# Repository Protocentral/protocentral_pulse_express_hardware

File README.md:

# ProtoCentral Pulse Express — Hardware

Open-source hardware design files for the **ProtoCentral Pulse Express** pulse-oximetry / heart-rate breakout — pairing the [Maxim MAX30102](https://www.analog.com/en/products/max30102.html) optical sensor with the [Maxim MAX32664D](https://www.analog.com/en/products/max32664.html) biometric sensor hub.

Unlike our [Pulse](https://github.com/Protocentral/protocentral_pulse_hardware) board, which streams raw PPG for the host to process, Pulse Express runs Maxim's algorithms on the MAX32664D hub itself and returns computed heart rate, SpO₂, and blood-pressure-trend estimates over I²C. That offloads the signal processing from your MCU at the cost of visibility into the raw signal.

## Links

| | |
|---|---|
| 🛒 Product page | https://protocentral.com/product/pulse-express-pulse-ox-heart-rate-sensor-with-max32664/ |
| 💻 Arduino library | https://github.com/Protocentral/protocentral-pulse-express |
| 📄 Sensor hub datasheet (Analog Devices / Maxim) | https://www.analog.com/media/en/technical-documentation/data-sheets/MAX32664.pdf |
| 📄 Optical sensor datasheet | https://www.analog.com/media/en/technical-documentation/data-sheets/MAX30102.pdf |

## Specifications

- **Sensor hub:** Maxim MAX32664GTGD+ (MAX32664D variant) with 32.768 kHz crystal
- **Optical sensor:** Maxim MAX30102 — red (660 nm) + IR (880 nm) LEDs, photodiode, and AFE
- **Output:** computed heart rate, SpO₂, and blood-pressure trend from the on-hub algorithms
- **Interface:** I²C, via 2× TXS0102 bidirectional level translators
- **Connector:** 6-pin 0.1″ header
- **Supply:** onboard AP2112K-3.3 V and AP2112K-1.8 V LDOs
- **Board:** 36.0 × 17.5 mm, 2-layer

## Revisions

| Revision | Design files | Notes |
|---|---|---|
| **v3** (current) | [`hardware/`](hardware/) | KiCad 10 |
| earlier | [`protocentral-pulse-express/hardware/`](https://github.com/Protocentral/protocentral-pulse-express/tree/master/hardware) | Eagle; retained in the Arduino library repository so existing links keep working |

## Repository layout

| Folder | Contents |
|---|---|
| [`hardware/`](hardware/) | KiCad project (schematic + PCB layout) and the exported [schematic PDF](hardware/protocentral-pulse-express-v3-schematic.pdf) |

## Important notice

This device is intended for research, education, and evaluation use only. It is **not** a medical diagnostic instrument and is not FDA, CE, or FCC approved for consumer use. The blood-pressure-trend output of the MAX32664D requires per-user calibration and is not a substitute for a validated blood-pressure monitor.

## License

The hardware design files in this repository are licensed under the **CERN Open Hardware Licence Version 2 – Permissive (CERN-OHL-P v2)**. See [LICENSE](LICENSE).

The accompanying firmware/library (in the separate [protocentral-pulse-express](https://github.com/Protocentral/protocentral-pulse-express) repository) is licensed under the MIT License.

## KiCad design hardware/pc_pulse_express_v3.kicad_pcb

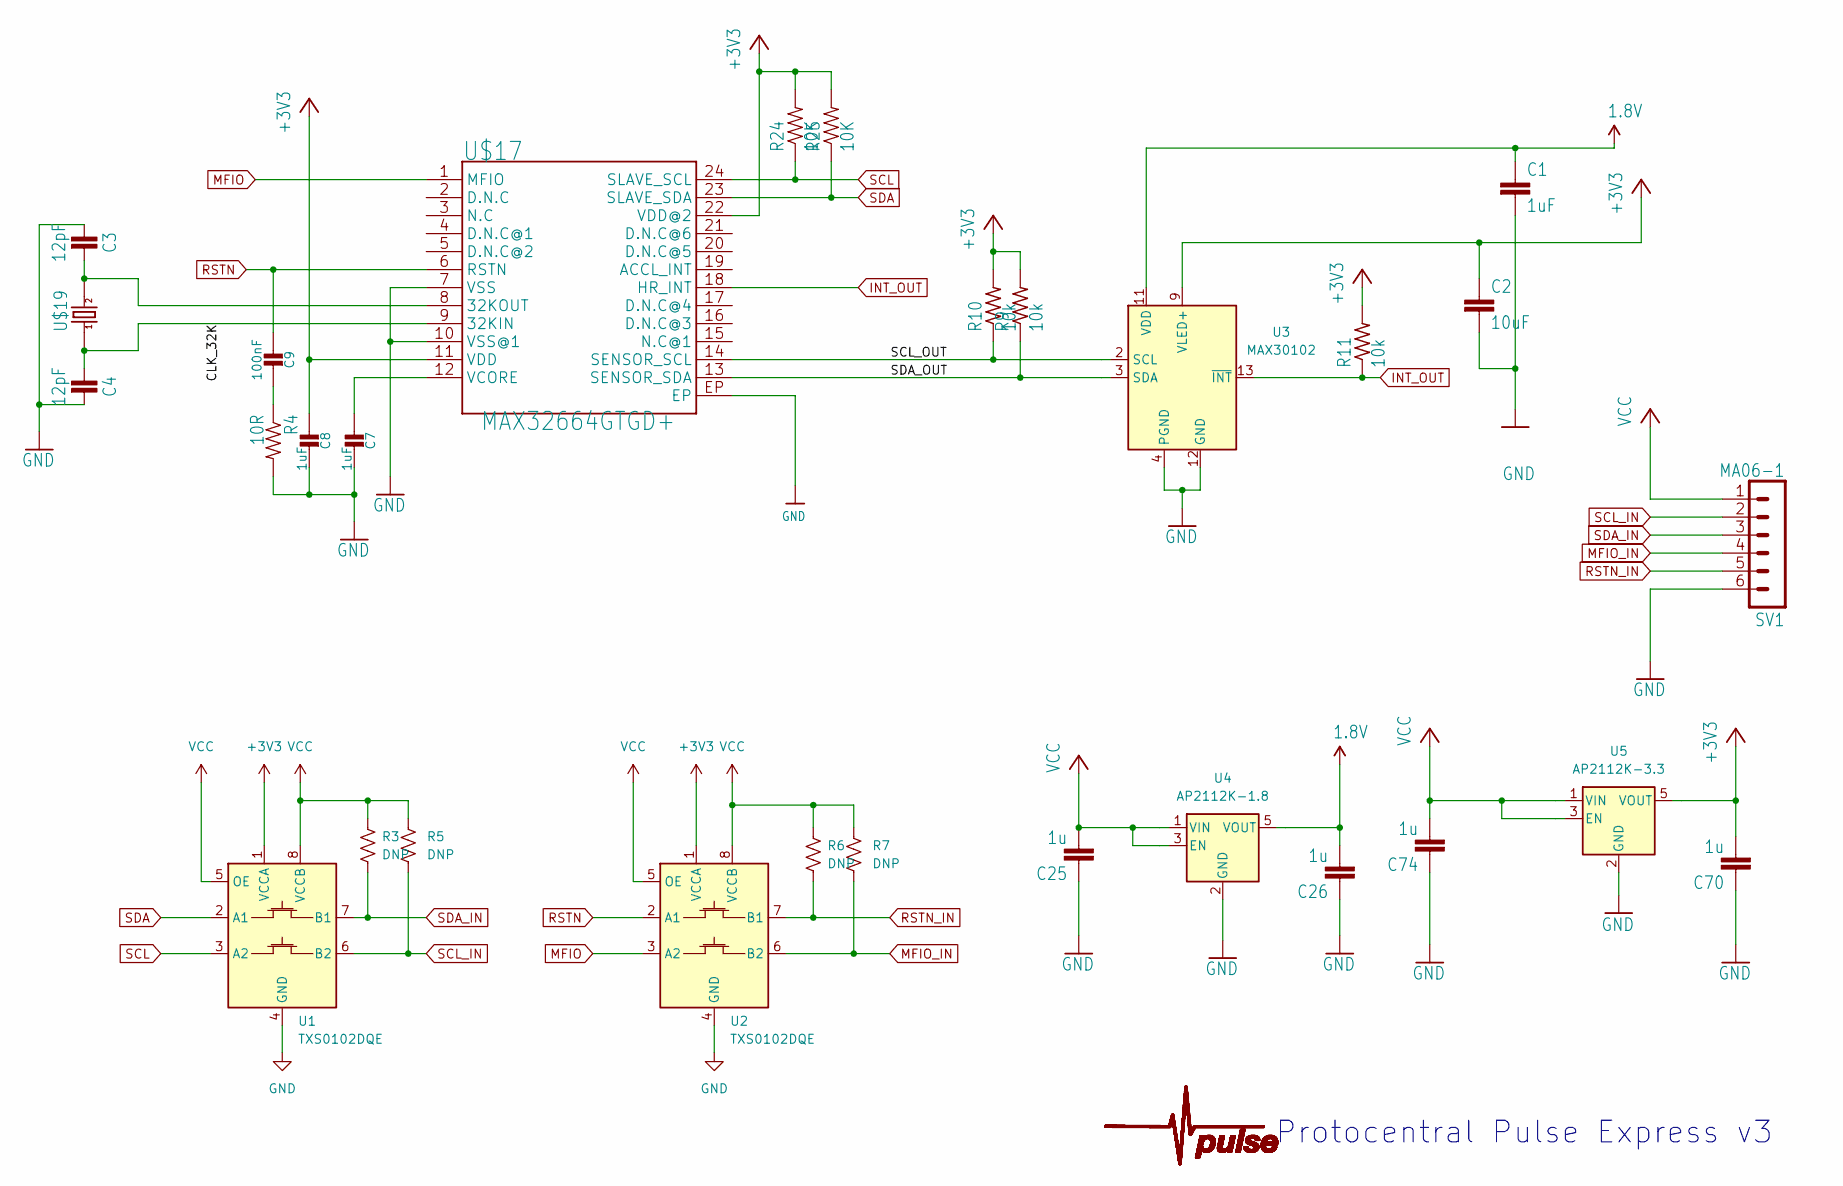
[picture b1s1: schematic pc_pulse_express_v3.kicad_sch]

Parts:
C1, C7, C8: 1uF; C_0402_1005Metric_Pad0.74x0.62mm_HandSolder
C2: 10uF; C_0402_1005Metric_Pad0.74x0.62mm_HandSolder
C3, C4: 12pF; C_0402_1005Metric_Pad0.74x0.62mm_HandSolder
C9: 100nF; C_0402_1005Metric_Pad0.74x0.62mm_HandSolder
C25, C26, C70, C74: 1u; C_0402_1005Metric_Pad0.74x0.62mm_HandSolder
R3, R5, R6, R7: DNP; R_0402_1005Metric_Pad0.72x0.64mm_HandSolder
R4: 10R; R_0402_1005Metric_Pad0.72x0.64mm_HandSolder
R9, R10, R11: 10k; R_0402_1005Metric_Pad0.72x0.64mm_HandSolder
R24, R25: 10K; R_0402_1005Metric_Pad0.72x0.64mm_HandSolder
SV1: MA06-1
U1, U2: TXS0102DQE; X2SON-8_1.4x1mm_P0.35mm
U3: MAX30102; Maxim_OLGA-14_3.3x5.6mm_P0.8mm
U4: AP2112K-1.8; SOT-23-5
U5: AP2112K-3.3; SOT-23-5
U$4: PULSE; PULSESMALL
U$17: MAX32664GTGD+; TQFN-24L
U$19: 520-327-12.5-34B(32.768KHZ); ECX-31B

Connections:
1.8V: C1.1, C26.2, U3.11 (VDD), U4.5 (VOUT)
+3V3: C2.1, C8.1, C70.2, R9.2, R10.2, R11.2, R24.2, R25.2, U1.1 (VCCA), U2.1 (VCCA), U3.9 (VLED+), U3.10 (VLED+), U5.5 (VOUT), U$17.11 (VDD), U$17.22 (VDD@2); also elsewhere on the board
/CLK_32K: C4.1, U$17.9 (32KIN), U$19.P$1 (1); also elsewhere on the board
/SCL_OUT: R10.1, U3.2 (SCL), U$17.14 (SENSOR_SCL)
/SDA_OUT: R9.1, U3.3 (SDA), U$17.13 (SENSOR_SDA)
GND: C1.2, C2.2, C3.1, C4.2, C7.2, C8.2, C25.1, C26.1, C70.1, C74.1, R4.2, SV1.6, U1.4 (GND), U2.4 (GND), U3.4 (PGND), U3.12 (GND), U4.2 (GND), U5.2 (GND), U$17.7 (VSS), U$17.10 (VSS@1), U$17.EP; also elsewhere on the board
INT_OUT: R11.1, U3.13 (~INT), U$17.18 (HR_INT)
MFIO: U2.3 (A2), U$17.1 (MFIO)
MFIO_IN: R7.2, SV1.4, U2.6 (B2)
unnamed: C9.2, R4.1
unnamed: C3.2, U$17.8 (32KOUT), U$19.P$2 (2)
unnamed: C7.1, U$17.12 (VCORE)
RSTN: C9.1, U2.2 (A1), U$17.6 (RSTN)
RSTN_IN: R6.2, SV1.5, U2.7 (B1)
SCL: R24.1, U1.3 (A2), U$17.24 (SLAVE_SCL)
SCL_IN: R5.2, SV1.2, U1.6 (B2)
SDA: R25.1, U1.2 (A1), U$17.23 (SLAVE_SDA)
SDA_IN: R3.2, SV1.3, U1.7 (B1)
VCC: C25.2, C74.2, R3.1, R5.1, R6.1, R7.1, SV1.1, U1.5 (OE), U1.8 (VCCB), U2.5 (OE), U2.8 (VCCB), U4.1 (VIN), U4.3 (EN), U5.1 (VIN), U5.3 (EN)

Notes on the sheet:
Protocentral Pulse Express v3

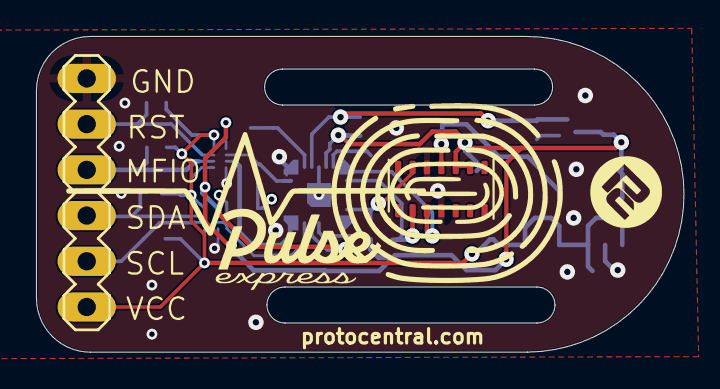
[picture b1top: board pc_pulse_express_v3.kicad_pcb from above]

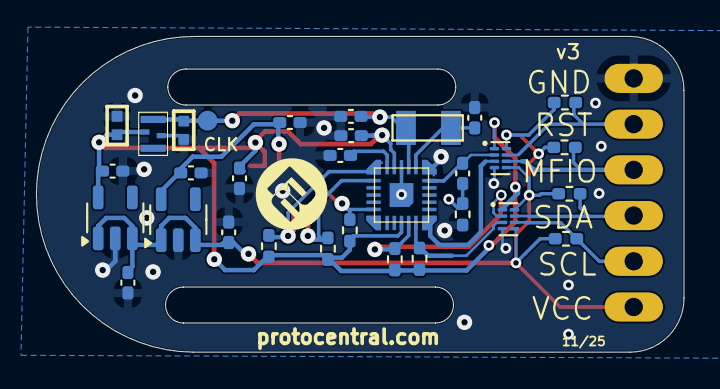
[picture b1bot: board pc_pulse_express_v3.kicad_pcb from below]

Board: 2 copper layers, 36.0 x 17.5 mm, 34 parts (31 on the bottom side), 19 nets.

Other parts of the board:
C14: 1uF; _0402
C15: 22pF; _0402
SWIO1: TPSQTP11R; TP11R_385
U$29: SIT1533AI-H4-DCC-32.768E; SIT1533

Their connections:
+3V3: C14.1, U$29.4 (VDD); also elsewhere on the board
/CLK_32K: C15.1, SWIO1.TP, U$29.3 (CLK); also elsewhere on the board
GND: C14.2, C15.2, U$29.2 (GND); also elsewhere on the board
